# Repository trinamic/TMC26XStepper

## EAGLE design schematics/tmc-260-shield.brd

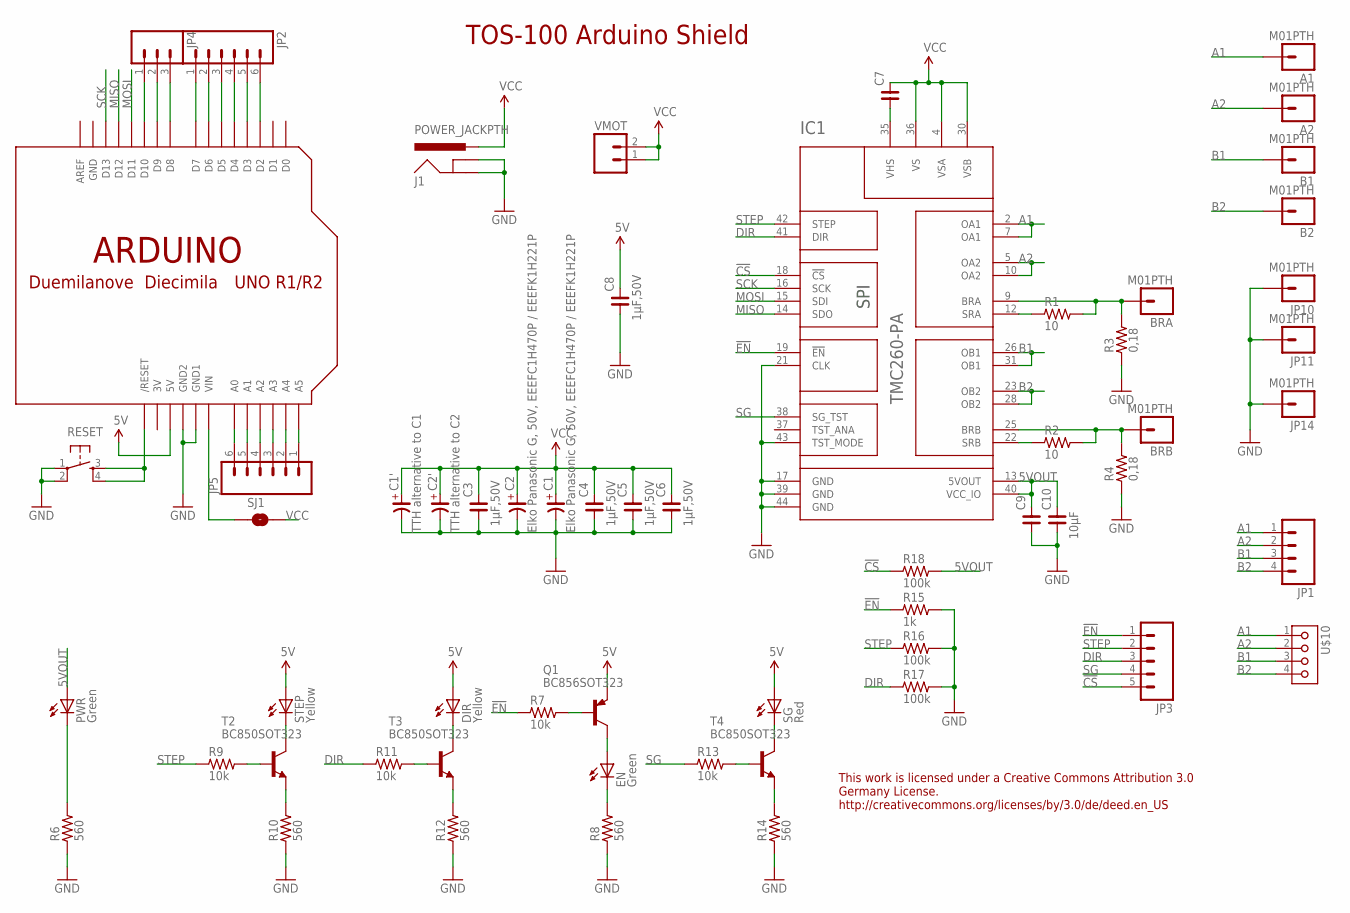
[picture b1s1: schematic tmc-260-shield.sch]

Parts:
A1, A2: M01PTH; 1X01
B1, B2: M01PTH; 1X01
BRA: M01PTH; 1X01
BRB: M01PTH; 1X01
C1, C2: Elko Panasonic G, 50V, EEEFC1H470P / EEEFK1H221P; CSV-G
C1': TTH alternative to C1; CE-035X100
C2': TTH alternative to C2; CE-035X100
C3, C4, C5, C8: 1µF,50V; C0603
C6: 1µF,50V; C1206
C7, C9: C_0603; C0603
C10: 10µF; C0603
DIR: Yellow; MICRO-SIDELED
EN: Green; MICRO-SIDELED
IC1: TMC260-PA; PQFP44_WITH_PADS
J1: POWER_JACKPTH; POWER_JACK_PTH
JP1: M04SCREW; SCREWTERMINAL-3.5MM-4
JP2, JP5: M06SIP; 1X06
JP3: M05PTH; 1X05
JP4: M03PTH; 1X03
JP10, JP11, JP14: M01PTH; 1X01
PWR: Green; MICRO-SIDELED
Q1: BC856SOT323; SOT323-BEC
R1, R2: 10; R0603
R3, R4: 0,18; R2512
R6, R8, R10, R12, R14: 560; R0603
R7, R9, R11, R13: 10k; R0603
R15: 1k; R0603
R16, R17, R18: 100k; R0603
RESET: TAC_SWITCHSMD; TACTILE_SWITCH_SMD
SG: Red; MICRO-SIDELED
SJ1: SOLDERJUMPERNO; SJ_2S-NO
STEP: Yellow; MICRO-SIDELED
T2, T3, T4: BC850SOT323; SOT323-BEC
U$1: ARDUINOUNO; ARDUINO
U$10: KK4H; KK-H-4
VMOT: M021X02_NO_SILK; 1X02_NO_SILK

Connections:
3V: U$1.3V
5V: C8.2, DIR.A, Q1.E, SG.A, STEP.A, U$1.5V
5VOUT: C9.2, C10.2, IC1.13 (5VOUT), IC1.40 (VCC_IO), PWR.A, R18.2
!CS: IC1.18 (!CS), JP3.5, R18.1
!EN: IC1.19 (!EN), JP3.1, R7.1, R15.1
A1: A1.1, IC1.2 (OA1), IC1.7 (OA1), JP1.1, U$10.1
A2: A2.1, IC1.5 (OA2), IC1.10 (OA2), JP1.2, U$10.2
B1: B1.1, IC1.26 (OB1), IC1.31 (OB1), JP1.3, U$10.3
B2: B2.1, IC1.23 (OB2), IC1.28 (OB2), JP1.4, U$10.4
DIR: IC1.41 (DIR), JP3.3, R11.1, R17.1
GND: C1.-, C1'.-, C2.-, C2'.-, C3.1, C4.1, C5.1, C6.1, C8.1, C9.1, C10.1, IC1.17 (GND), IC1.21 (CLK), IC1.39 (GND), IC1.43 (TST_MODE), IC1.44 (GND), J1.GND, J1.GNDBREAK, JP10.1, JP11.1, JP14.1, R3.1, R4.1, R6.1, R8.1, R10.1, R12.1, R14.1, R15.2, R16.2, R17.2, RESET.1, RESET.2, U$1.GND, U$1.GND1, U$1.GND2
MISO: IC1.14 (SDO), U$1.D12
MOSI: IC1.15 (SDI), U$1.D11
unnamed: JP4.1, U$1.D10
unnamed: JP4.2, U$1.D9
unnamed: JP4.3, U$1.D8
unnamed: JP2.1, U$1.D7
unnamed: JP2.2, U$1.D6
unnamed: JP2.3, U$1.D5
unnamed: JP2.4, U$1.D4
unnamed: JP2.5, U$1.D3
unnamed: JP2.6, U$1.D2
unnamed: JP5.1, U$1.A5
unnamed: JP5.2, U$1.A4
unnamed: JP5.3, U$1.A3
unnamed: JP5.4, U$1.A2
unnamed: JP5.5, U$1.A1
unnamed: JP5.6, U$1.A0
unnamed: R9.2, T2.B
unnamed: RESET.3, RESET.4, U$1.RESET (/RESET)
unnamed: SJ1.1, U$1.VIN
unnamed: STEP.C, T2.C
unnamed: R10.2, T2.E
unnamed: PWR.C, R6.2
unnamed: R11.2, T3.B
unnamed: DIR.C, T3.C
unnamed: R12.2, T3.E
unnamed: EN.A, Q1.C
unnamed: BRA.1, IC1.9 (BRA), R1.2, R3.2
unnamed: IC1.12 (SRA), R1.1
unnamed: BRB.1, IC1.25 (BRB), R2.2, R4.2
unnamed: IC1.22 (SRB), R2.1
unnamed: EN.C, R8.2
unnamed: Q1.B, R7.2
unnamed: R13.2, T4.B
unnamed: SG.C, T4.C
unnamed: R14.2, T4.E
SCK: IC1.16 (SCK), U$1.D13
SG: IC1.38 (SG_TST), JP3.4, R13.1
STEP: IC1.42 (STEP), JP3.2, R9.1, R16.1
VCC: C1.+, C1'.+, C2.+, C2'.+, C3.2, C4.2, C5.2, C6.2, C7.2, IC1.4 (VSA), IC1.30 (VSB), IC1.36 (VS), J1.PWR, SJ1.2, VMOT.1, VMOT.2
VHS: C7.1, IC1.35 (VHS)

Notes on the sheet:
TOS-100 Arduino Shield
This work is licensed under a Creative Commons Attribution 3.0 Germany License. http://creativecommons.org/licenses/by/3.0/de/deed.en_US

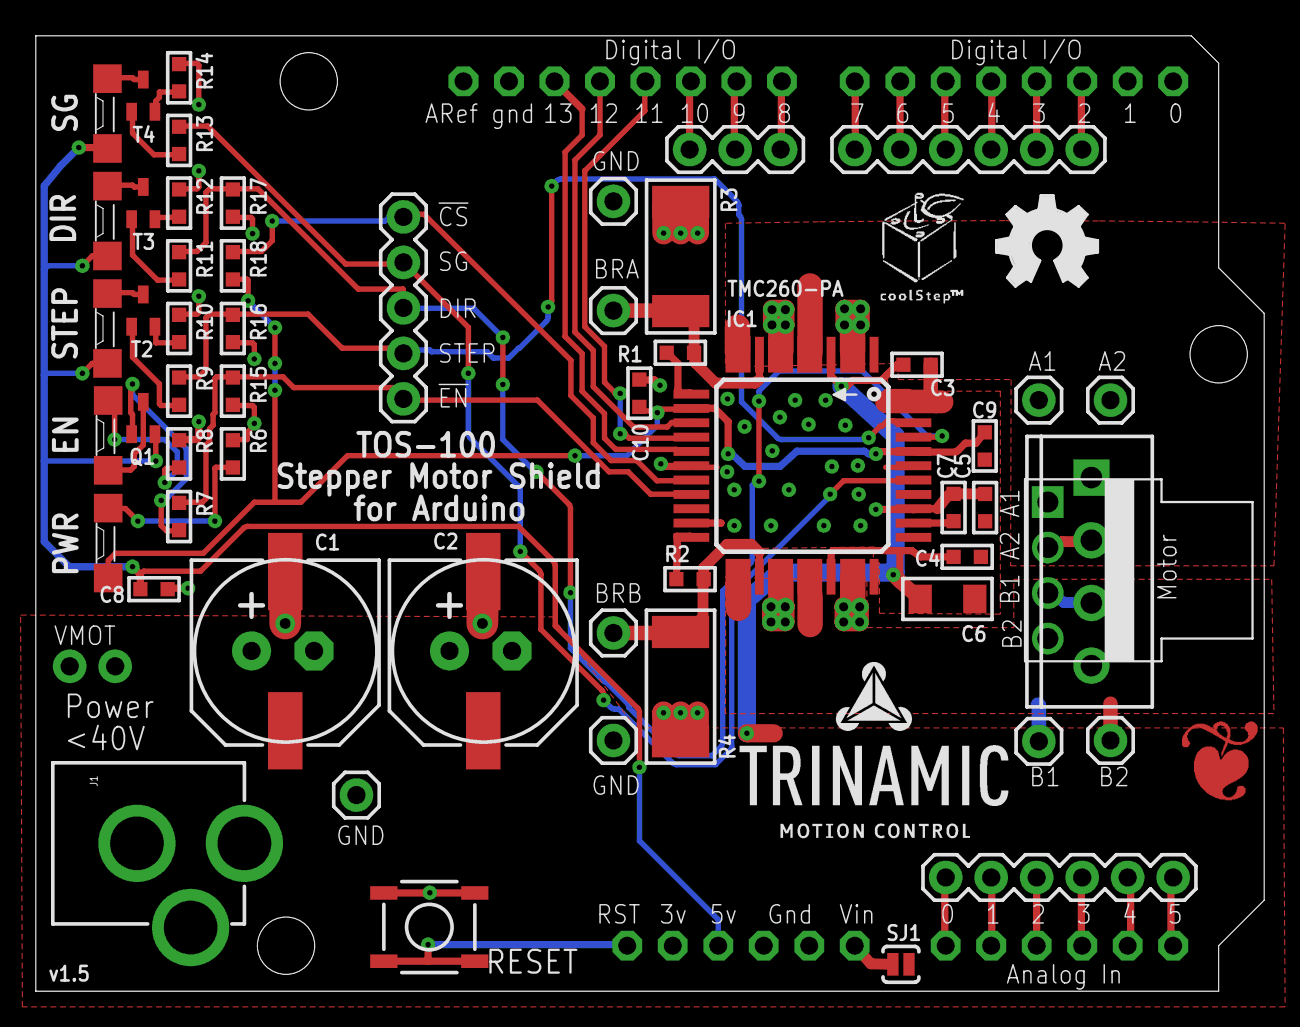
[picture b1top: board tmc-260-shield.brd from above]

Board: 2 copper layers, 68.6 x 53.3 mm, 64 parts (0 on the bottom side), 51 nets.

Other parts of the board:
U$5: LOGO
U$9: COOLSTEP
U$11: OSHW_FILLX200_NOTEXT
U$12: SMALL_LOGO_COPPER
U$13: QR-TMC-100-BOTTOM-BIG

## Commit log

2012-11-21 one readme is enough
2013-01-31 now with schematics
2013-01-31 First pages commit
2013-02-14 adding capacitor values
2013-02-23 Fixed some capacitor values
    C6: changed value from 1µF to 10µF
    C7: added value 1µF
    C9: added value 1µF
    C10: changed from 10µF to 1µF
2013-02-23 ignore eagle backup files
2014-01-31 hmm, this does not work in processing 2.0
    old processing version seemed to have default imports … now fixed
2015-11-15 FIx the registers that coolstep setup writes to, used to update the wrong register.
2016-02-19 fix for rollover of micros() during move.
2016-11-16 fixed to build and run with ControlP5 2.2.5
2018-04-09 Move Arduino.h #include directive to TMC26XStepper.h
    TMC26XStepper.h uses the non-standard boolean type which is defined in the Arduino core library. The use of this type in TMC26XStepper.h relied on Arduino.h having been included externally before TMC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
2020-01-25 Add library to PlatformIO Registry, v1.0.0
